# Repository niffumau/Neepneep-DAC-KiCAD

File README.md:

# Neepneep DAC

This is the version that plays audio from a flash chip.

## V1
My original prototype, working with the Attiny85 and the winbond W25Q32 flash chip.

## V2

V2 is currently a work in progress, i'm trying bring the cost down so i'm trying to switch over to a smaller flash and move over to a different chip so this one will not program the Attiny85

I'm looking at the Attiny412 and the 8mbit version of the flash chip.

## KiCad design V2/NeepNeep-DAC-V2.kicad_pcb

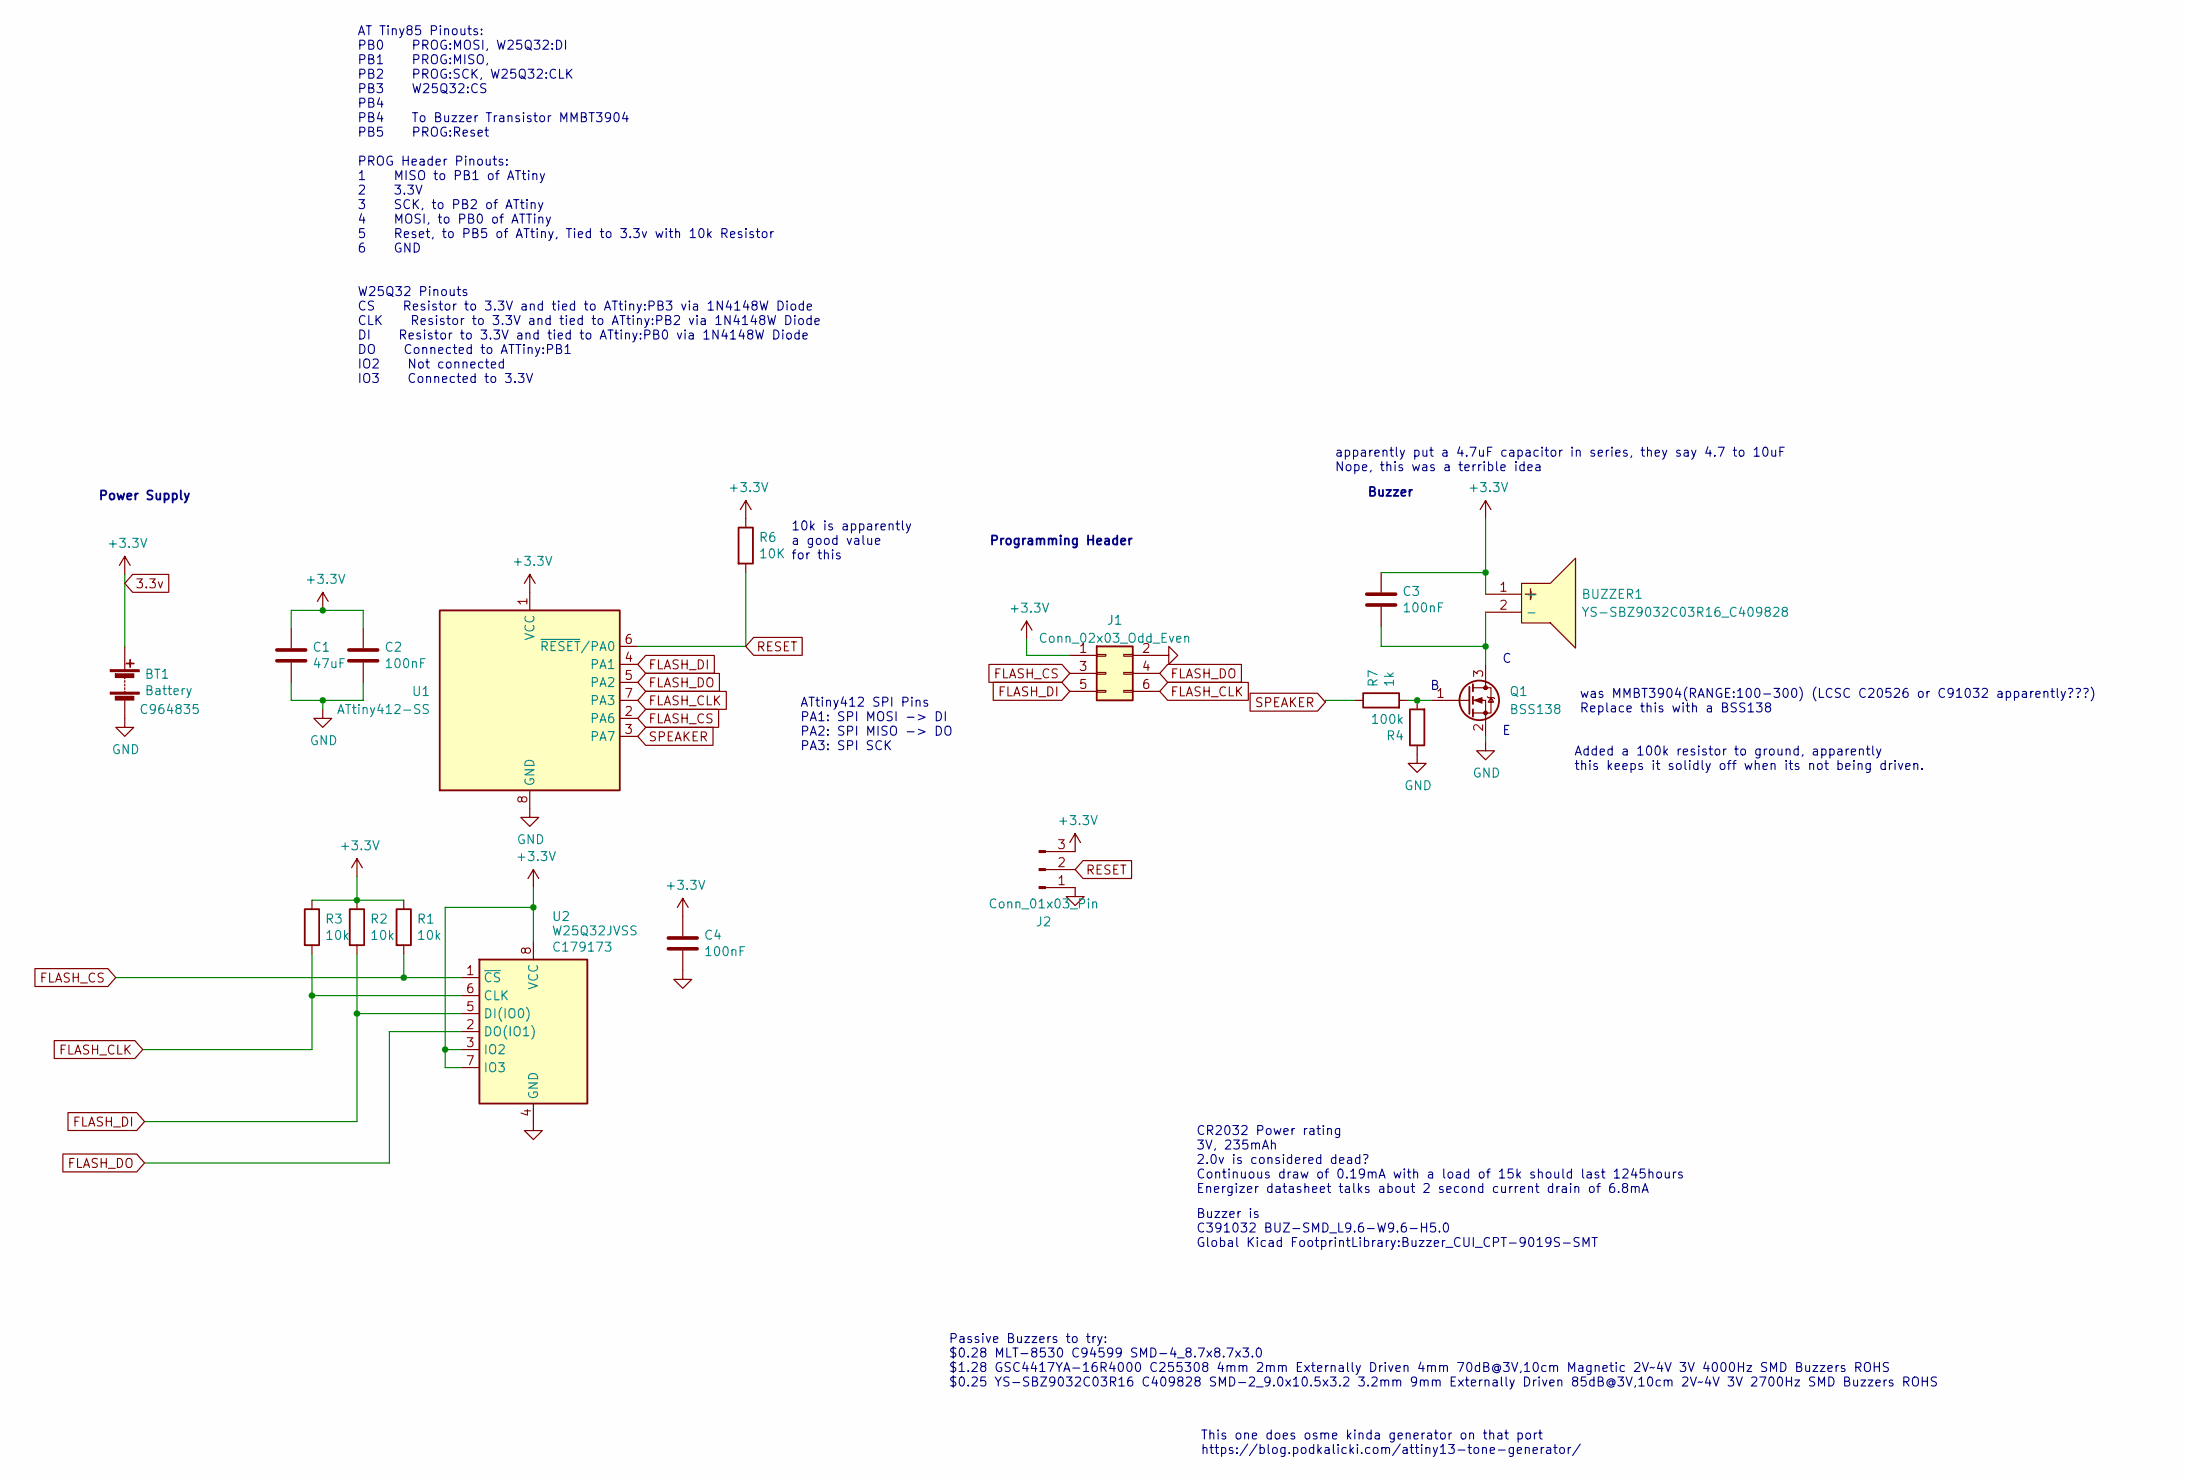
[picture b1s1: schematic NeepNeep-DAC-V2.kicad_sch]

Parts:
BT1: Battery; BatteryHolder_SMD_TAB_2032; LCSC C964835
BUZZER1: YS-SBZ9032C03R16_C409828; BUZ-SMD_FUET-9025-XXV; LCSC Part C409828
C1: 47uF; C_0805_2012Metric
C2, C3, C4: 100nF; C_0805_2012Metric
J1: Conn_02x03_Odd_Even; SPI-Header_1x06_P1.27mm
J2: Conn_01x03_Pin; UPDI PinHeader_1x03_P1.27mm_Vertical
Q1: BSS138; SOT-23
R1, R2, R3: 10k; R_0805_2012Metric
R4: 100k; R_0805_2012Metric
R6: 10K; R_0805_2012Metric
R7: 1k; R_0805_2012Metric
U1: ATtiny412-SS; SOIC-8_3.9x4.9mm_P1.27mm
U2: W25Q32JVSS; SOIC-8_5.23x5.23mm_P1.27mm; LCSC C179173

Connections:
3.3v: BT1.1 (+), BUZZER1.1 (+), C1.1, C2.1, C3.1, C4.1, J1.1, J2.3, R1.1, R2.1, R3.1, R6.1, U1.1 (VCC), U2.3 (IO2), U2.7 (IO3), U2.8 (VCC)
FLASH_CLK: J1.6, R3.2, U1.7 (PA3), U2.6 (CLK)
FLASH_CS: J1.3, R1.2, U1.2 (PA6), U2.1 (~CS)
FLASH_DI: J1.5, R2.2, U1.4 (PA1), U2.5 (DI(IO0))
FLASH_DO: J1.4, U1.5 (PA2), U2.2 (DO(IO1))
GND: BT1.2 (-), C1.2, C2.2, C4.2, J1.2, J2.1, Q1.2 (S), R4.1, U1.8 (GND), U2.4 (GND)
unnamed: BUZZER1.2 (-), C3.2, Q1.3 (D)
unnamed: Q1.1 (G), R4.2, R7.2
RESET: J2.2, R6.2, U1.6 (~RESET/PA0)
SPEAKER: R7.1, U1.3 (PA7)

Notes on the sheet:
apparently put a 4.7uF capacitor in series, they say 4.7 to 10uF Nope, this was a terrible idea
This one does osme kinda generator on that port https://blog.podkalicki.com/attiny13-tone-generator/
Programming Header
ATtiny412 SPI Pins PA1: SPI MOSI -> DI PA2: SPI MISO -> DO PA3: SPI SCK
Buzzer is C391032 BUZ-SMD_L9.6-W9.6-H5.0 Global Kicad FootprintLibrary:Buzzer_CUI_CPT-9019S-SMT
Added a 100k resistor to ground, apparently this keeps it solidly off when its not being driven.
Buzzer
AT Tiny85 Pinouts: PB0 PROG:MOSI, W25Q32:DI PB1 PROG:MISO, PB2 PROG:SCK, W25Q32:CLK PB3 W25Q32:CS PB4 PB4 To Buzzer Transistor MMBT3904 PB5 PROG:Reset PROG Header Pinouts: 1 MISO to PB1 of ATtiny 2 3.3V 3 SCK, to PB2 of ATtiny 4 MOSI, to PB0 of ATTiny 5 Reset, to PB5 of ATtiny, Tied to 3.3v with 10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
CR2032 Power rating 3V, 235mAh 2.0v is considered dead? Continuous draw of 0.19mA with a load of 15k should last 1245hours Energizer datasheet talks about 2 second current drain of 6.8mA
Passive Buzzers to try: $0.28 MLT-8530 C94599 SMD-4_8.7x8.7x3.0 $1.28 GSC4417YA-16R4000 C255308 4mm 2mm Externally Driven 4mm 70dB@3V,10cm Magnetic 2V~4V 3V 4000Hz SMD Buzzers ROHS $0.25 YS-SBZ9032C03R16 C409828 SMD-2_9.0x10.5x3.2 3.2mm 9mm Externally Driven 85dB@3V,10cm 2V~4V 3V 2700Hz SMD Buzzers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
Power Supply
10k is apparently a good value for this
was MMBT3904(RANGE:100-300) (LCSC C20526 or C91032 apparently???) Replace this with a BSS138

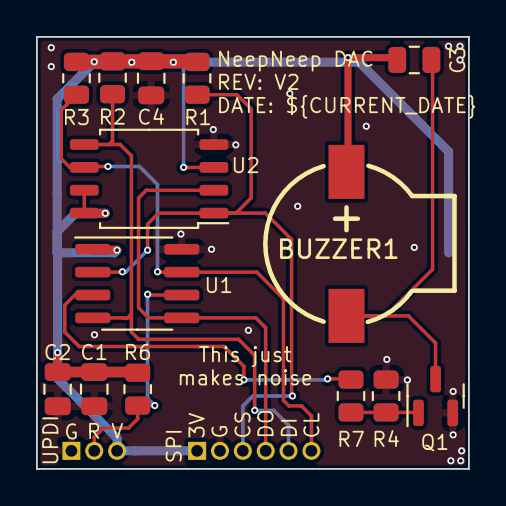
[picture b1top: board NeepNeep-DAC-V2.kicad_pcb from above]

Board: 2 copper layers, 24.0 x 24.0 mm, 17 parts (1 on the bottom side), 10 nets.

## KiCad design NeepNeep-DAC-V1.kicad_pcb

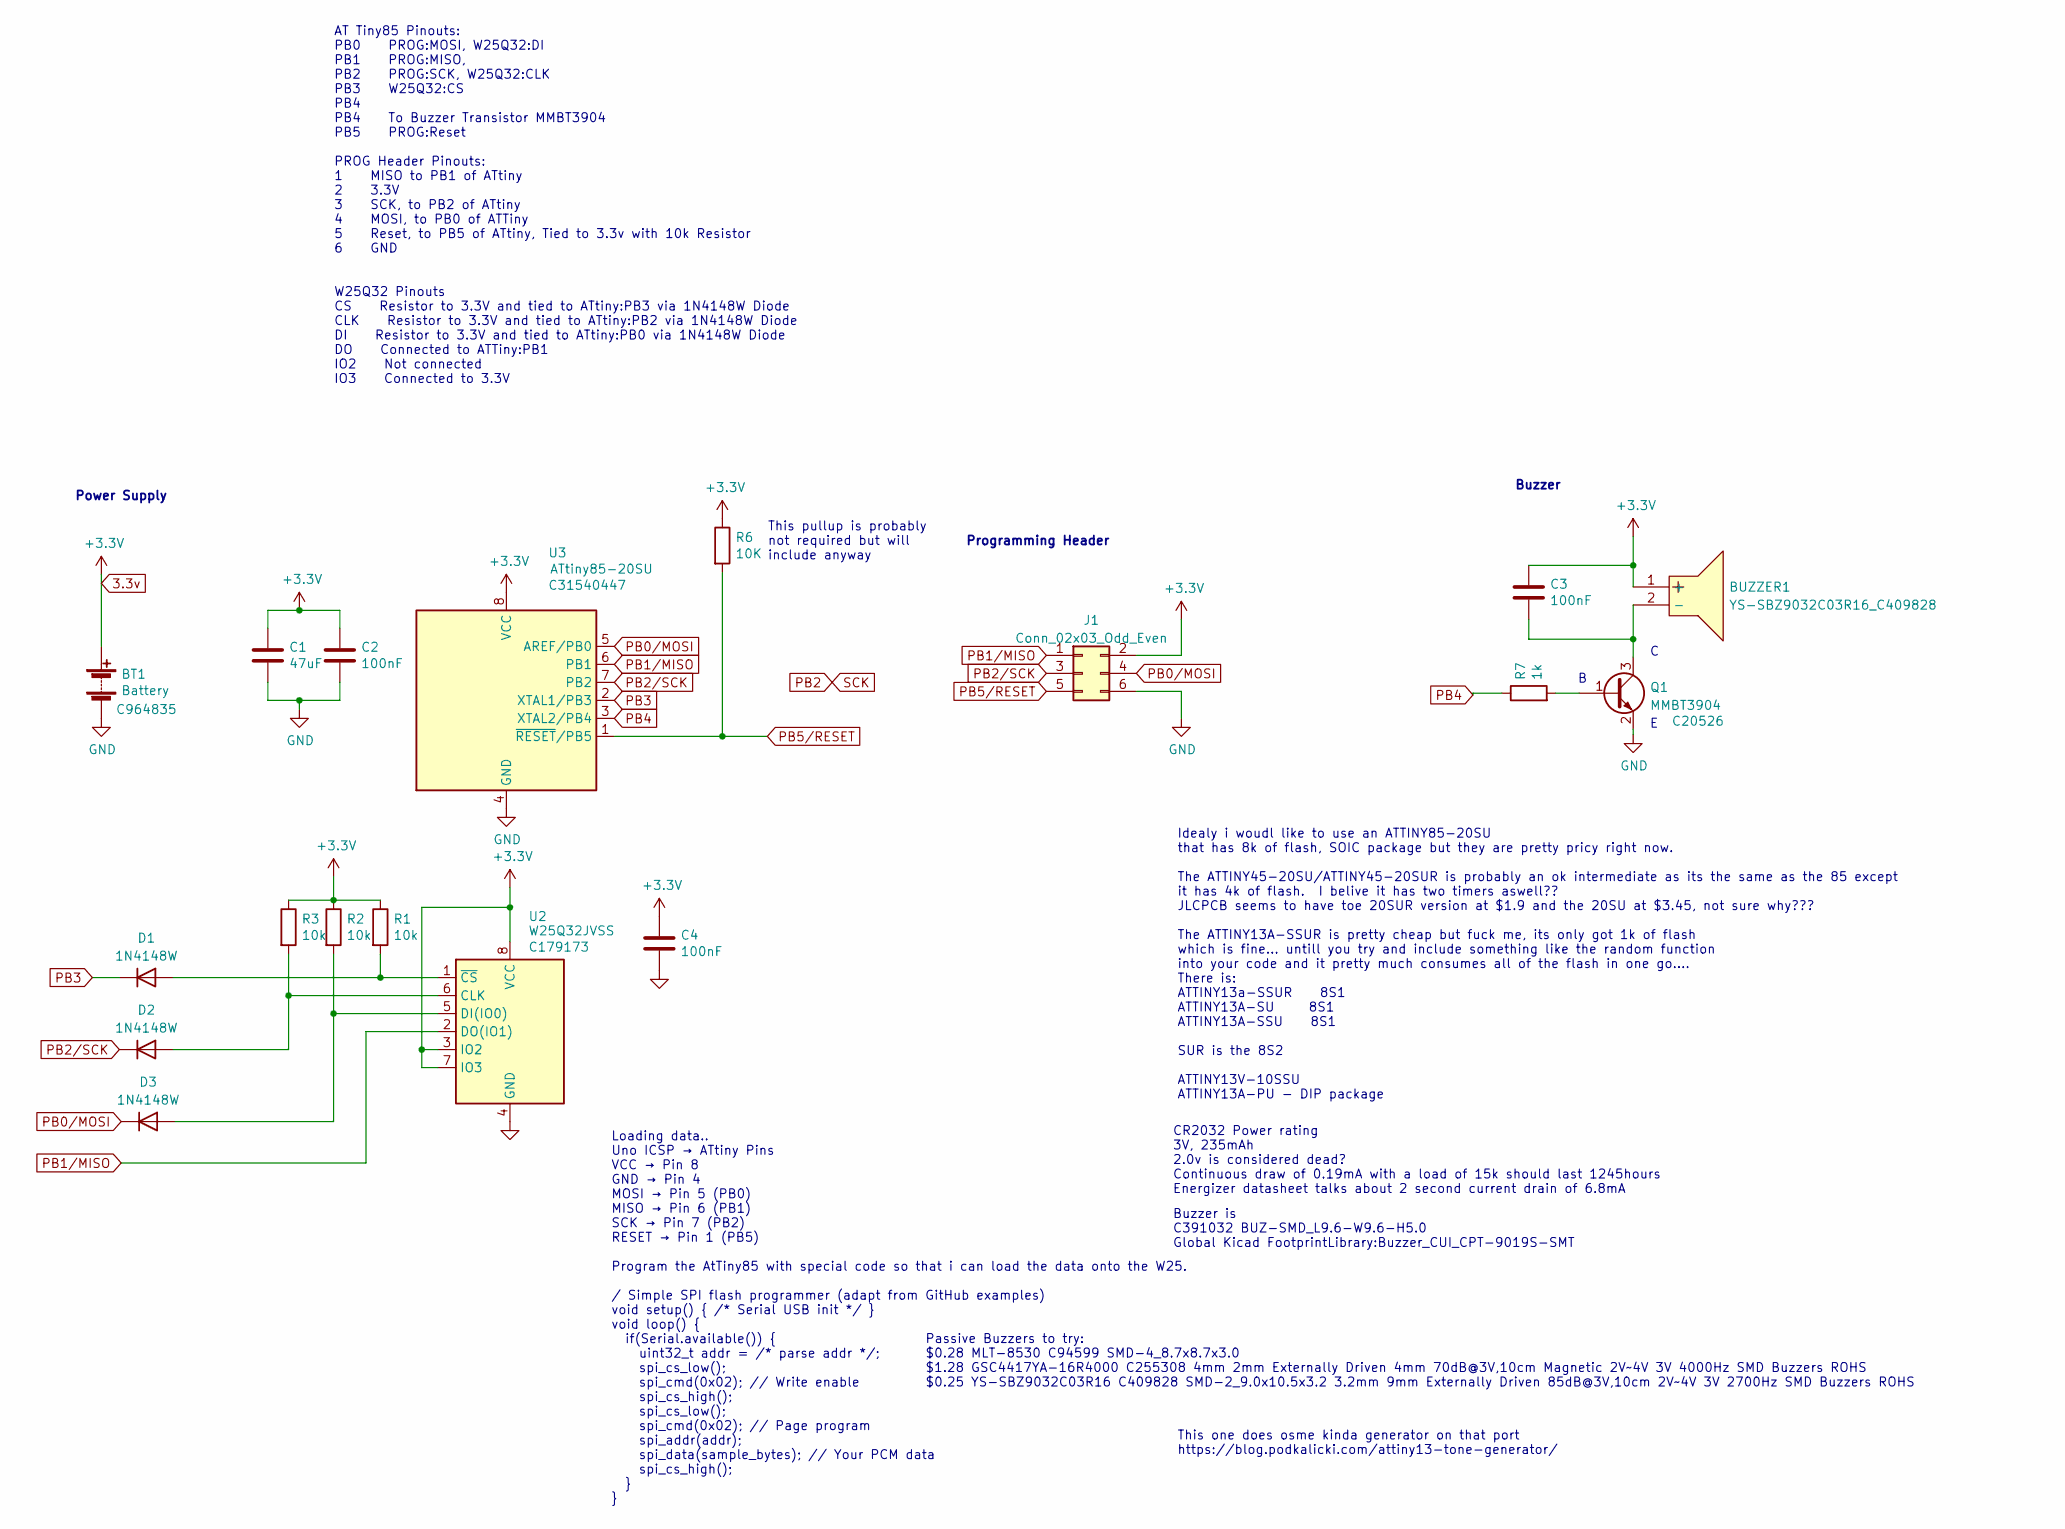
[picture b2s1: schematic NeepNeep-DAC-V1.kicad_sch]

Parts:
BT1: Battery; BatteryHolder_SMD_TAB_2032; LCSC C964835
BUZZER1: YS-SBZ9032C03R16_C409828; BUZ-SMD_FUET-9025-XXV; LCSC Part C409828
C1: 47uF; C_0805_2012Metric
C2, C3, C4: 100nF; C_0805_2012Metric
D1, D2, D3: 1N4148W; D_SOD-123
J1: Conn_02x03_Odd_Even; PRG-Header_1x06_P1.27mm
Q1: MMBT3904; SOT-23; LCSC C20526
R1, R2, R3: 10k; R_0805_2012Metric
R6: 10K; R_0805_2012Metric
R7: 1k; R_0805_2012Metric
U2: W25Q32JVSS; SOIC-8_5.23x5.23mm_P1.27mm; LCSC C179173
U3: ATtiny85-20SU; SOIC-8W_5.3x5.3mm_P1.27mm; LCSC C31540447

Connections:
3.3v: BT1.1 (+), BUZZER1.1 (+), C1.1, C2.1, C3.1, C4.1, J1.2, R1.1, R2.1, R3.1, R6.1, U2.3 (IO2), U2.7 (IO3), U2.8 (VCC), U3.8 (VCC)
GND: BT1.2 (-), C1.2, C2.2, C4.2, J1.6, Q1.2 (E), U2.4 (GND), U3.4 (GND)
unnamed: BUZZER1.2 (-), C3.2, Q1.3 (C)
unnamed: D1.2 (A), R1.2, U2.1 (~CS)
unnamed: D2.2 (A), R3.2, U2.6 (CLK)
unnamed: D3.2 (A), R2.2, U2.5 (DI(IO0))
unnamed: Q1.1 (B), R7.2
PB0/MOSI: D3.1 (K), J1.4, U3.5 (AREF/PB0)
PB1/MISO: J1.1, U2.2 (DO(IO1)), U3.6 (PB1)
PB2/SCK: D2.1 (K), J1.3, U3.7 (PB2)
PB3: D1.1 (K), U3.2 (XTAL1/PB3)
PB4: R7.1, U3.3 (XTAL2/PB4)
PB5/RESET: J1.5, R6.2, U3.1 (~RESET/PB5)

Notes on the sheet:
This one does osme kinda generator on that port https://blog.podkalicki.com/attiny13-tone-generator/
Programming Header
Buzzer is C391032 BUZ-SMD_L9.6-W9.6-H5.0 Global Kicad FootprintLibrary:Buzzer_CUI_CPT-9019S-SMT
Idealy i woudl like to use an ATTINY85-20SU that has 8k of flash, SOIC package but they are pretty pricy right now. The ATTINY45-20SU/ATTINY45-20SUR is probably an ok intermediate as its the same as the 85 except it has 4k of flash. I belive it has two timers aswell?? JLCPCB seems to have toe 20SUR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
Buzzer
Loading data.. Uno ICSP → ATtiny Pins VCC → Pin 8 GND → Pin 4 MOSI → Pin 5 (PB0) MISO → Pin 6 (PB1) SCK → Pin 7 (PB2) RESET → Pin 1 (PB5) Program the AtTiny85 with special code so that i can load the data onto the W25. / Simple SPI flash programmer (adapt from GitHub examples) void setup() { /* Ser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
AT Tiny85 Pinouts: PB0 PROG:MOSI, W25Q32:DI PB1 PROG:MISO, PB2 PROG:SCK, W25Q32:CLK PB3 W25Q32:CS PB4 PB4 To Buzzer Transistor MMBT3904 PB5 PROG:Reset PROG Header Pinouts: 1 MISO to PB1 of ATtiny 2 3.3V 3 SCK, to PB2 of ATtiny 4 MOSI, to PB0 of ATTiny 5 Reset, to PB5 of ATtiny, Tied to 3.3v with 10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
CR2032 Power rating 3V, 235mAh 2.0v is considered dead? Continuous draw of 0.19mA with a load of 15k should last 1245hours Energizer datasheet talks about 2 second current drain of 6.8mA
Passive Buzzers to try: $0.28 MLT-8530 C94599 SMD-4_8.7x8.7x3.0 $1.28 GSC4417YA-16R4000 C255308 4mm 2mm Externally Driven 4mm 70dB@3V,10cm Magnetic 2V~4V 3V 4000Hz SMD Buzzers ROHS $0.25 YS-SBZ9032C03R16 C409828 SMD-2_9.0x10.5x3.2 3.2mm 9mm Externally Driven 85dB@3V,10cm 2V~4V 3V 2700Hz SMD Buzzers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
Power Supply
This pullup is probably not required but will include anyway

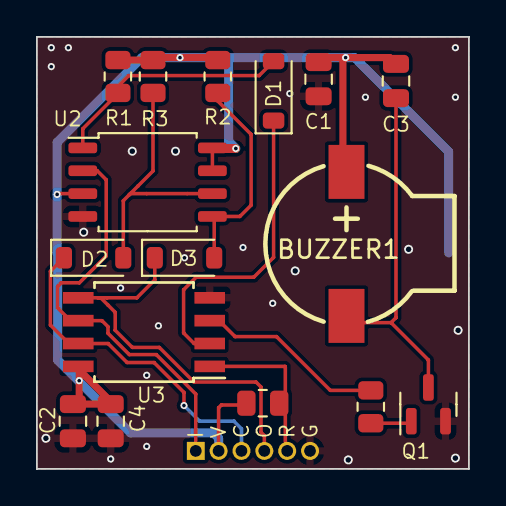
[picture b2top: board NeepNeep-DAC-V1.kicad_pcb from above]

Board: 2 copper layers, 24.0 x 24.0 mm, 18 parts (1 on the bottom side), 13 nets.

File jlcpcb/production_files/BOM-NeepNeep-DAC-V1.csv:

Comment,Designator,Footprint,LCSC
W25Q32JVSS,U2,SOIC-8_5.23x5.23mm_P1.27mm,C179173
MMBT3904,Q1,SOT-23,C20526
ATtiny85-20SU,U3,SOIC-8W_5.3x5.3mm_P1.27mm,C31540447
YS-SBZ9032C03R16_C409828,BUZZER1,BUZ-SMD_FUET-9025-XXV,C409828
100nF,C4,C_0805_2012Metric,
100nF,C3,C_0805_2012Metric,
10k,R3,R_0805_2012Metric,
10k,R2,R_0805_2012Metric,
10k,R1,R_0805_2012Metric,
1N4148W,D3,D_SOD-123,
1N4148W,D2,D_SOD-123,
1N4148W,D1,D_SOD-123,
47uF,C1,C_0805_2012Metric,
10K,R6,R_0805_2012Metric,
100nF,C2,C_0805_2012Metric,
1k,R7,R_0805_2012Metric,

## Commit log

2026-01-20 Commit: A .gitignore A NeepNeep-DAC-V1.kicad_pcb A NeepNeep-DAC-V1.kicad_prl A NeepNeep-DAC-V1.kicad_pro A NeepNeep-DAC-V1.kicad_sch A bom/ibom.html A fp-info-cache A jlcpcb/gerber/NeepNeep-DAC-V1-Cu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
2026-02-05 Commit: M NeepNeep-DAC-V1.kicad_sch
2026-02-05 Commit: M NeepNeep-DAC-V1.kicad_sch A V2/NeepNeep-DAC-V2-backups/NeepNeep-DAC-V2-2026-02-05_161125.zip A V2/NeepNeep-DAC-V2-backups/NeepNeep-DAC-V2-2026-02-05_170153.zip A V2/NeepNeep-DAC-V2.kicad_pc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
2026-02-09 Commit: A V2/NeepNeep-DAC-V2-backups/NeepNeep-DAC-V2-2026-02-06_155723.zip A V2/NeepNeep-DAC-V2-backups/NeepNeep-DAC-V2-2026-02-06_161052.zip A V2/NeepNeep-DAC-V2-backups/NeepNeep-DAC-V2-2026-02-06_1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
2026-02-11 Commit: A V2/NeepNeep-DAC-V2-backups/NeepNeep-DAC-V2-2026-02-09_174934.zip A V2/NeepNeep-DAC-V2-backups/NeepNeep-DAC-V2-2026-02-10_125359.zip A V2/NeepNeep-DAC-V2-backups/NeepNeep-DAC-V2-2026-02-10_1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
2026-02-11 Commit: A V2/NeepNeep-DAC-V2-backups/NeepNeep-DAC-V2-2026-02-11_154859.zip A V2/NeepNeep-DAC-V2-backups/NeepNeep-DAC-V2-2026-02-11_164151.zip A V2/NeepNeep-DAC-V2-backups/NeepNeep-DAC-V2-2026-02-11_1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
2026-02-12 Commit: M README.md A V2/NeepNeep-DAC-V2-backups/NeepNeep-DAC-V2-2026-02-12_124743.zip A V2/NeepNeep-DAC-V2-backups/NeepNeep-DAC-V2-2026-02-12_132550.zip A V2/NeepNeep-DAC-V2-backups/NeepNeep-DAC-V2-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
2026-02-12 Commit: D V2/NeepNeep-DAC-V2-backups/NeepNeep-DAC-V2-2026-02-12_124743.zip A V2/NeepNeep-DAC-V2-backups/NeepNeep-DAC-V2-2026-02-12_170828.zip
2026-02-13 Commit: D V2/NeepNeep-DAC-V2-backups/NeepNeep-DAC-V2-2026-02-12_132550.zip A V2/NeepNeep-DAC-V2-backups/NeepNeep-DAC-V2-2026-02-13_132614.zip A V2/NeepNeep-DAC-V2-backups/NeepNeep-DAC-V2-2026-02-13_1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
2026-02-13 Commit: D V2/NeepNeep-DAC-V2-backups/NeepNeep-DAC-V2-2026-02-13_132614.zip D V2/NeepNeep-DAC-V2-backups/NeepNeep-DAC-V2-2026-02-13_133905.zip D V2/NeepNeep-DAC-V2-backups/NeepNeep-DAC-V2-2026-02-13_1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
2026-03-12 Commit: D V2/NeepNeep-DAC-V2-backups/NeepNeep-DAC-V2-2026-02-13_141833.zip A V2/NeepNeep-DAC-V2-backups/NeepNeep-DAC-V2-2026-02-16_160315.zip A V2/NeepNeep-DAC-V2-backups/NeepNeep-DAC-V2-2026-03-12_1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
